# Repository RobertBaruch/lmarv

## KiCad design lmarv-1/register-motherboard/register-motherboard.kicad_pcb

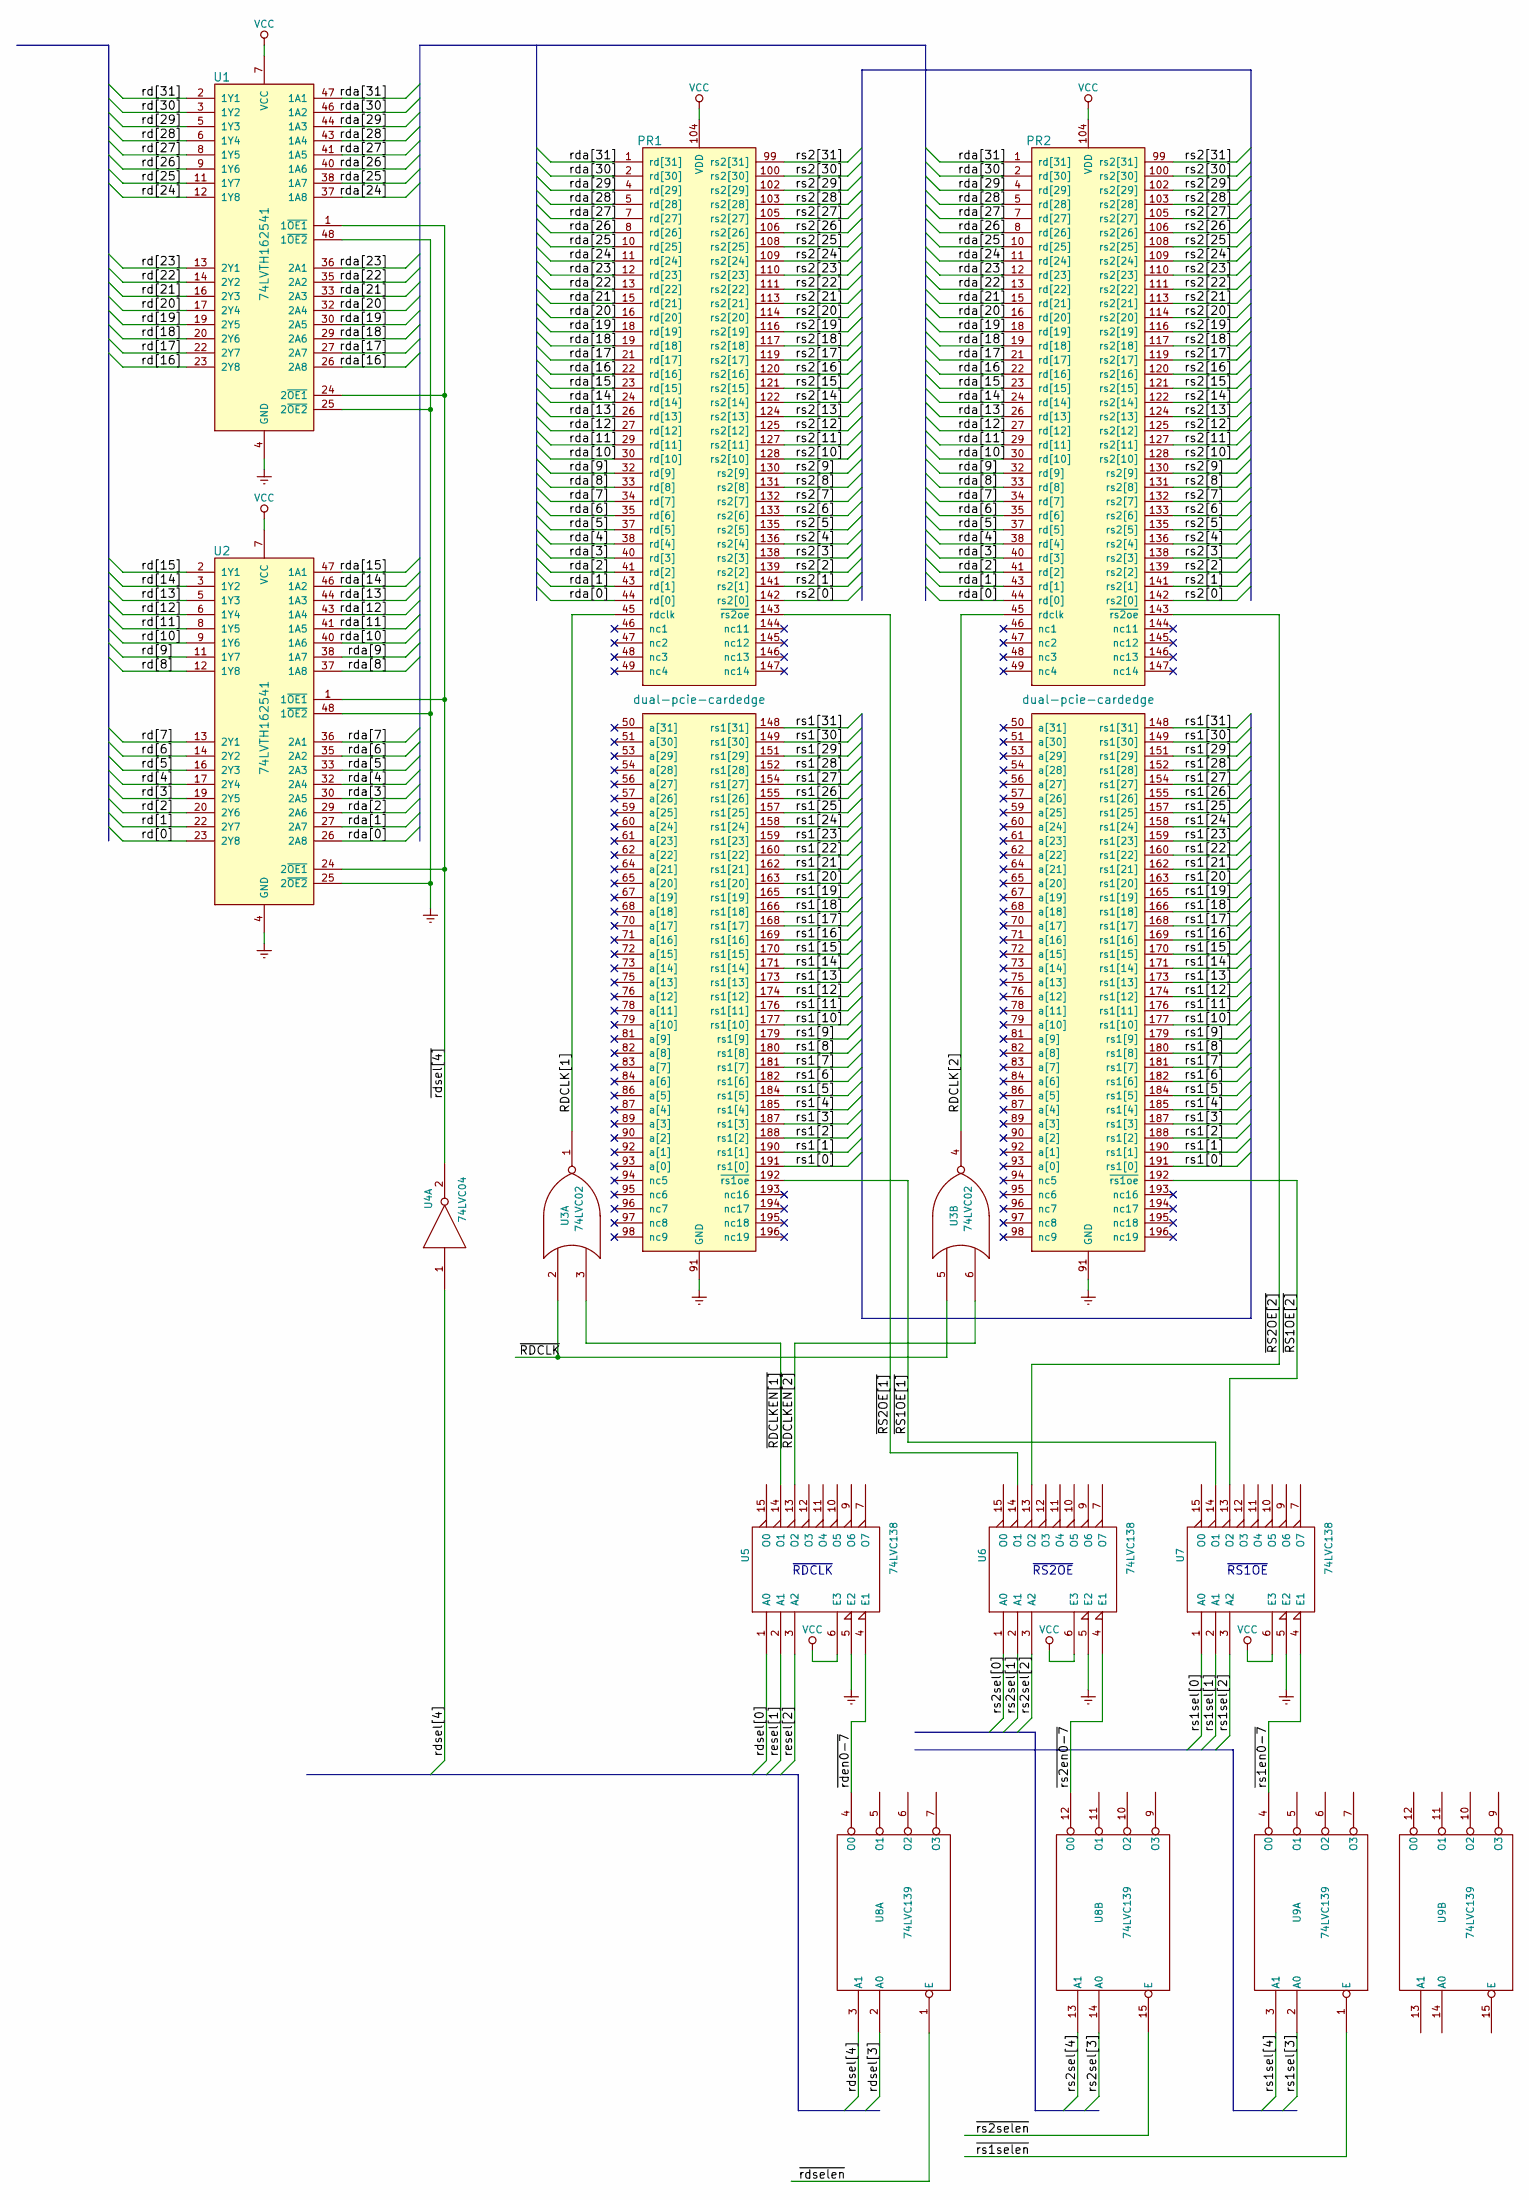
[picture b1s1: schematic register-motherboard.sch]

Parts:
PR1, PR2: dual-pcie-cardedge; 2pci_express_slot
U1, U2: 74LVTH162541; SSOP-48_7.5x15.9mm_Pitch0.635mm
U3: 74LVC02; SOIC-8_3.9x4.9mm_Pitch1.27mm
U4: 74LVC04; SO-4_4.4x2.3mm_Pitch1.27mm
U5, U6, U7: 74LVC138; SOIC-16_3.9x9.9mm_Pitch1.27mm
U8, U9: 74LVC139; SOIC-16_3.9x9.9mm_Pitch1.27mm

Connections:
/RDCLK[1]: PR1.45 (rdclk), U3.1
/RDCLK[2]: PR2.45 (rdclk), U3.4
/rd[0]: U2.23 (2Y8)
/rd[1]: U2.22 (2Y7)
/rd[2]: U2.20 (2Y6)
/rd[3]: U2.19 (2Y5)
/rd[4]: U2.17 (2Y4)
/rd[5]: U2.16 (2Y3)
/rd[6]: U2.14 (2Y2)
/rd[7]: U2.13 (2Y1)
/rd[8]: U2.12 (1Y8)
/rd[9]: U2.11 (1Y7)
/rd[10]: U2.9 (1Y6)
/rd[11]: U2.8 (1Y5)
/rd[12]: U2.6 (1Y4)
/rd[13]: U2.5 (1Y3)
/rd[14]: U2.3 (1Y2)
/rd[15]: U2.2 (1Y1)
/rd[16]: U1.23 (2Y8)
/rd[17]: U1.22 (2Y7)
/rd[18]: U1.20 (2Y6)
/rd[19]: U1.19 (2Y5)
/rd[20]: U1.17 (2Y4)
/rd[21]: U1.16 (2Y3)
/rd[22]: U1.14 (2Y2)
/rd[23]: U1.13 (2Y1)
/rd[24]: U1.12 (1Y8)
/rd[25]: U1.11 (1Y7)
/rd[26]: U1.9 (1Y6)
/rd[27]: U1.8 (1Y5)
/rd[28]: U1.6 (1Y4)
/rd[29]: U1.5 (1Y3)
/rd[30]: U1.3 (1Y2)
/rd[31]: U1.2 (1Y1)
/rda[0]: PR1.44 (rd[0]), PR2.44 (rd[0]), U2.26 (2A8)
/rda[1]: PR1.43 (rd[1]), PR2.43 (rd[1]), U2.27 (2A7)
/rda[2]: PR1.41 (rd[2]), PR2.41 (rd[2]), U2.29 (2A6)
/rda[3]: PR1.40 (rd[3]), PR2.40 (rd[3]), U2.30 (2A5)
/rda[4]: PR1.38 (rd[4]), PR2.38 (rd[4]), U2.32 (2A4)
/rda[5]: PR1.37 (rd[5]), PR2.37 (rd[5]), U2.33 (2A3)
/rda[6]: PR1.35 (rd[6]), PR2.35 (rd[6]), U2.35 (2A2)
/rda[7]: PR1.34 (rd[7]), PR2.34 (rd[7]), U2.36 (2A1)
/rda[8]: PR1.33 (rd[8]), PR2.33 (rd[8]), U2.37 (1A8)
/rda[9]: PR1.32 (rd[9]), PR2.32 (rd[9]), U2.38 (1A7)
/rda[10]: PR1.30 (rd[10]), PR2.30 (rd[10]), U2.40 (1A6)
/rda[11]: PR1.29 (rd[11]), PR2.29 (rd[11]), U2.41 (1A5)
/rda[12]: PR1.27 (rd[12]), PR2.27 (rd[12]), U2.43 (1A4)
/rda[13]: PR1.26 (rd[13]), PR2.26 (rd[13]), U2.44 (1A3)
/rda[14]: PR1.24 (rd[14]), PR2.24 (rd[14]), U2.46 (1A2)
/rda[15]: PR1.23 (rd[15]), PR2.23 (rd[15]), U2.47 (1A1)
/rda[16]: PR1.22 (rd[16]), PR2.22 (rd[16]), U1.26 (2A8)
/rda[17]: PR1.21 (rd[17]), PR2.21 (rd[17]), U1.27 (2A7)
/rda[18]: PR1.19 (rd[18]), PR2.19 (rd[18]), U1.29 (2A6)
/rda[19]: PR1.18 (rd[19]), PR2.18 (rd[19]), U1.30 (2A5)
/rda[20]: PR1.16 (rd[20]), PR2.16 (rd[20]), U1.32 (2A4)
/rda[21]: PR1.15 (rd[21]), PR2.15 (rd[21]), U1.33 (2A3)
/rda[22]: PR1.13 (rd[22]), PR2.13 (rd[22]), U1.35 (2A2)
/rda[23]: PR1.12 (rd[23]), PR2.12 (rd[23]), U1.36 (2A1)
/rda[24]: PR1.11 (rd[24]), PR2.11 (rd[24]), U1.37 (1A8)
/rda[25]: PR1.10 (rd[25]), PR2.10 (rd[25]), U1.38 (1A7)
/rda[26]: PR1.8 (rd[26]), PR2.8 (rd[26]), U1.40 (1A6)
/rda[27]: PR1.7 (rd[27]), PR2.7 (rd[27]), U1.41 (1A5)
/rda[28]: PR1.5 (rd[28]), PR2.5 (rd[28]), U1.43 (1A4)
/rda[29]: PR1.4 (rd[29]), PR2.4 (rd[29]), U1.44 (1A3)
/rda[30]: PR1.2 (rd[30]), PR2.2 (rd[30]), U1.46 (1A2)
/rda[31]: PR1.1 (rd[31]), PR2.1 (rd[31]), U1.47 (1A1)
/rdsel[0]: U5.1 (A0)
/rdsel[3]: U8.2 (A0)
/rdsel[4]: U4.1, U8.3 (A1)
/resel[1]: U5.2 (A1)
/resel[2]: U5.3 (A2)
/rs1[0]: PR1.191 (rs1[0]), PR2.191 (rs1[0])
/rs1[1]: PR1.190 (rs1[1]), PR2.190 (rs1[1])
/rs1[2]: PR1.188 (rs1[2]), PR2.188 (rs1[2])
/rs1[3]: PR1.187 (rs1[3]), PR2.187 (rs1[3])
/rs1[4]: PR1.185 (rs1[4]), PR2.185 (rs1[4])
/rs1[5]: PR1.184 (rs1[5]), PR2.184 (rs1[5])
/rs1[6]: PR1.182 (rs1[6]), PR2.182 (rs1[6])
/rs1[7]: PR1.181 (rs1[7]), PR2.181 (rs1[7])
/rs1[8]: PR1.180 (rs1[8]), PR2.180 (rs1[8])
/rs1[9]: PR1.179 (rs1[9]), PR2.179 (rs1[9])
/rs1[10]: PR1.177 (rs1[10]), PR2.177 (rs1[10])
/rs1[11]: PR1.176 (rs1[11]), PR2.176 (rs1[11])
/rs1[12]: PR1.174 (rs1[12]), PR2.174 (rs1[12])
/rs1[13]: PR1.173 (rs1[13]), PR2.173 (rs1[13])
/rs1[14]: PR1.171 (rs1[14]), PR2.171 (rs1[14])
/rs1[15]: PR1.170 (rs1[15]), PR2.170 (rs1[15])
/rs1[16]: PR1.169 (rs1[16]), PR2.169 (rs1[16])
/rs1[17]: PR1.168 (rs1[17]), PR2.168 (rs1[17])
/rs1[18]: PR1.166 (rs1[18]), PR2.166 (rs1[18])
/rs1[19]: PR1.165 (rs1[19]), PR2.165 (rs1[19])
/rs1[20]: PR1.163 (rs1[20]), PR2.163 (rs1[20])
/rs1[21]: PR1.162 (rs1[21]), PR2.162 (rs1[21])
/rs1[22]: PR1.160 (rs1[22]), PR2.160 (rs1[22])
/rs1[23]: PR1.159 (rs1[23]), PR2.159 (rs1[23])
/rs1[24]: PR1.158 (rs1[24]), PR2.158 (rs1[24])
/rs1[25]: PR1.157 (rs1[25]), PR2.157 (rs1[25])
/rs1[26]: PR1.155 (rs1[26]), PR2.155 (rs1[26])
/rs1[27]: PR1.154 (rs1[27]), PR2.154 (rs1[27])
/rs1[28]: PR1.152 (rs1[28]), PR2.152 (rs1[28])
/rs1[29]: PR1.151 (rs1[29]), PR2.151 (rs1[29])
/rs1[30]: PR1.149 (rs1[30]), PR2.149 (rs1[30])
/rs1[31]: PR1.148 (rs1[31]), PR2.148 (rs1[31])
/rs1sel[0]: U7.1 (A0)
/rs1sel[1]: U7.2 (A1)
/rs1sel[2]: U7.3 (A2)
/rs1sel[3]: U9.2 (A0)
/rs1sel[4]: U9.3 (A1)
/rs2[0]: PR1.142 (rs2[0]), PR2.142 (rs2[0])
/rs2[1]: PR1.141 (rs2[1]), PR2.141 (rs2[1])
/rs2[2]: PR1.139 (rs2[2]), PR2.139 (rs2[2])
/rs2[3]: PR1.138 (rs2[3]), PR2.138 (rs2[3])
/rs2[4]: PR1.136 (rs2[4]), PR2.136 (rs2[4])
/rs2[5]: PR1.135 (rs2[5]), PR2.135 (rs2[5])
/rs2[6]: PR1.133 (rs2[6]), PR2.133 (rs2[6])
/rs2[7]: PR1.132 (rs2[7]), PR2.132 (rs2[7])
/rs2[8]: PR1.131 (rs2[8]), PR2.131 (rs2[8])
/rs2[9]: PR1.130 (rs2[9]), PR2.130 (rs2[9])
/rs2[10]: PR1.128 (rs2[10]), PR2.128 (rs2[10])
/rs2[11]: PR1.127 (rs2[11]), PR2.127 (rs2[11])
/rs2[12]: PR1.125 (rs2[12]), PR2.125 (rs2[12])
/rs2[13]: PR1.124 (rs2[13]), PR2.124 (rs2[13])
/rs2[14]: PR1.122 (rs2[14]), PR2.122 (rs2[14])
/rs2[15]: PR1.121 (rs2[15]), PR2.121 (rs2[15])
/rs2[16]: PR1.120 (rs2[16]), PR2.120 (rs2[16])
/rs2[17]: PR1.119 (rs2[17]), PR2.119 (rs2[17])
/rs2[18]: PR1.117 (rs2[18]), PR2.117 (rs2[18])
/rs2[19]: PR1.116 (rs2[19]), PR2.116 (rs2[19])
/rs2[20]: PR1.114 (rs2[20]), PR2.114 (rs2[20])
/rs2[21]: PR1.113 (rs2[21]), PR2.113 (rs2[21])
/rs2[22]: PR1.111 (rs2[22]), PR2.111 (rs2[22])
/rs2[23]: PR1.110 (rs2[23]), PR2.110 (rs2[23])
/rs2[24]: PR1.109 (rs2[24]), PR2.109 (rs2[24])
/rs2[25]: PR1.108 (rs2[25]), PR2.108 (rs2[25])
/rs2[26]: PR1.106 (rs2[26]), PR2.106 (rs2[26])
/rs2[27]: PR1.105 (rs2[27]), PR2.105 (rs2[27])
/rs2[28]: PR1.103 (rs2[28]), PR2.103 (rs2[28])
/rs2[29]: PR1.102 (rs2[29]), PR2.102 (rs2[29])
/rs2[30]: PR1.100 (rs2[30]), PR2.100 (rs2[30])
/rs2[31]: PR1.99 (rs2[31]), PR2.99 (rs2[31])
/rs2sel[0]: U6.1 (A0)
/rs2sel[1]: U6.2 (A1)
/rs2sel[2]: U6.3 (A2)
/rs2sel[3]: U8.14 (A0)
/rs2sel[4]: U8.13 (A1)
/~RDCLK: U3.2, U3.5
/~RDCLKEN[1]: U3.3, U5.14 (O1)
/~RDCLKEN[2]: U3.6, U5.13 (O2)
/~RS1OE[1]: PR1.192 (~rs1oe), U7.14 (O1)
/~RS1OE[2]: PR2.192 (~rs1oe), U7.13 (O2)
/~RS2OE[1]: PR1.143 (~rs2oe), U6.14 (O1)
/~RS2OE[2]: PR2.143 (~rs2oe), U6.13 (O2)
/~rden0-7: U5.4 (E1), U8.4 (O0)
/~rdsel[4]: U1.1 (1~OE1), U1.24 (2~OE1), U2.1 (1~OE1), U2.24 (2~OE1), U4.2
/~rdselen: U8.1 (E)
/~rs1en0-7: U7.4 (E1), U9.4 (O0)
/~rs1selen: U9.1 (E)
/~rs2en0-7: U6.4 (E1), U8.12 (O0)
/~rs2selen: U8.15 (E)
GND: U3.7 (GND), U5.8 (GND), U6.8 (GND), U7.8 (GND), U8.8 (GND), U9.8 (GND)
GNDREF: PR1.3 (GND), PR1.9 (GND), PR1.14 (GND), PR1.20 (GND), PR1.25 (GND), PR1.31 (GND), PR1.36 (GND), PR1.42 (GND), PR1.52 (GND), PR1.58 (GND), PR1.63 (GND), PR1.69 (GND), PR1.74 (GND), PR1.80 (GND), PR1.85 (GND), PR1.91 (GND), PR1.101 (GND), PR1.107 (GND), PR1.112 (GND), PR1.118 (GND), PR1.123 (GND), PR1.129 (GND), PR1.134 (GND), PR1.140 (GND), PR1.150 (GND), PR1.156 (GND), PR1.161 (GND), PR1.167 (GND), PR1.172 (GND), PR1.178 (GND), PR1.183 (GND), PR1.189 (GND), PR2.3 (GND), PR2.9 (GND), PR2.14 (GND), PR2.20 (GND), PR2.25 (GND), PR2.31 (GND), PR2.36 (GND), PR2.42 (GND), PR2.52 (GND), PR2.58 (GND), PR2.63 (GND), PR2.69 (GND), PR2.74 (GND), PR2.80 (GND), PR2.85 (GND), PR2.91 (GND), PR2.101 (GND), PR2.107 (GND), PR2.112 (GND), PR2.118 (GND), PR2.123 (GND), PR2.129 (GND), PR2.134 (GND), PR2.140 (GND), PR2.150 (GND), PR2.156 (GND), PR2.161 (GND), PR2.167 (GND), PR2.172 (GND), PR2.178 (GND), PR2.183 (GND), PR2.189 (GND), U1.4 (GND), U1.10 (GND), U1.15 (GND), U1.21 (GND), U1.25 (2~OE2), U1.28 (GND), U1.34 (GND), U1.39 (GND), U1.45 (GND), U1.48 (1~OE2), U2.4 (GND), U2.10 (GND), U2.15 (GND), U2.21 (GND), U2.25 (2~OE2), U2.28 (GND), U2.34 (GND), U2.39 (GND), U2.45 (GND), U2.48 (1~OE2), U5.5 (E2), U6.5 (E2), U7.5 (E2)
VCC: PR1.6 (VDD), PR1.17 (VDD), PR1.28 (VDD), PR1.39 (VDD), PR1.55 (VDD), PR1.66 (VDD), PR1.77 (VDD), PR1.88 (VDD), PR1.104 (VDD), PR1.115 (VDD), PR1.126 (VDD), PR1.137 (VDD), PR1.153 (VDD), PR1.164 (VDD), PR1.175 (VDD), PR1.186 (VDD), PR2.6 (VDD), PR2.17 (VDD), PR2.28 (VDD), PR2.39 (VDD), PR2.55 (VDD), PR2.66 (VDD), PR2.77 (VDD), PR2.88 (VDD), PR2.104 (VDD), PR2.115 (VDD), PR2.126 (VDD), PR2.137 (VDD), PR2.153 (VDD), PR2.164 (VDD), PR2.175 (VDD), PR2.186 (VDD), U1.7 (VCC), U1.18 (VCC), U1.31 (VCC), U1.42 (VCC), U2.7 (VCC), U2.18 (VCC), U2.31 (VCC), U2.42 (VCC), U5.6 (E3), U5.16 (VCC), U6.6 (E3), U6.16 (VCC), U7.6 (E3), U7.16 (VCC), U8.16 (VCC), U9.16 (VCC)

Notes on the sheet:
~RS1OE
~RS2OE
~RDCLK

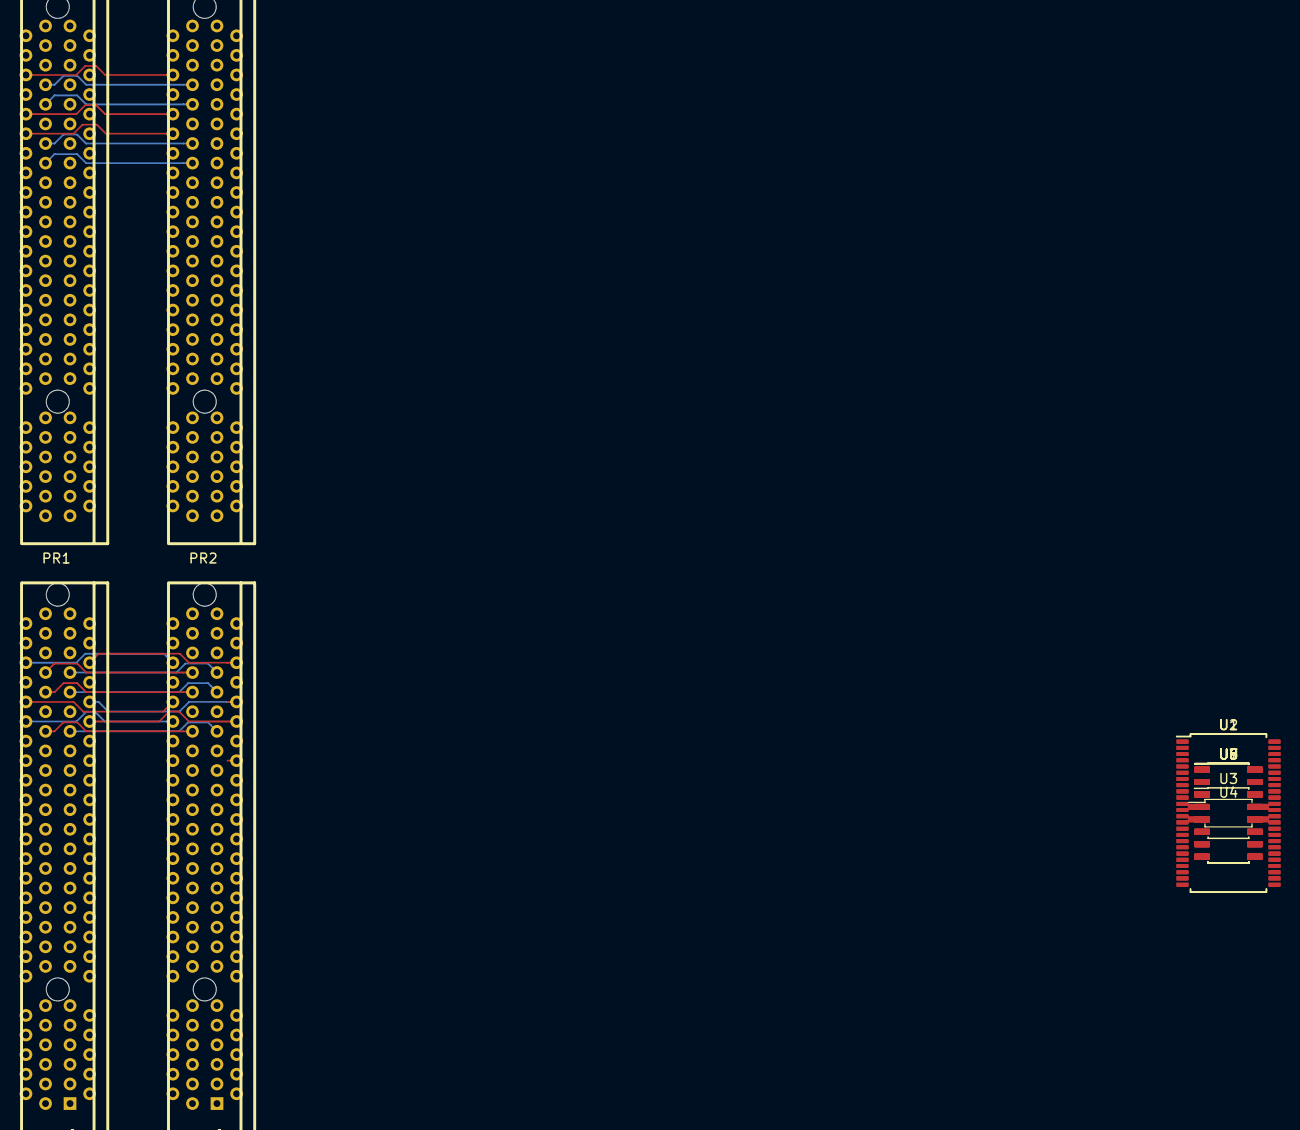
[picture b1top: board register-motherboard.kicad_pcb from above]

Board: 4 copper layers, 11 parts (0 on the bottom side), 113 nets.

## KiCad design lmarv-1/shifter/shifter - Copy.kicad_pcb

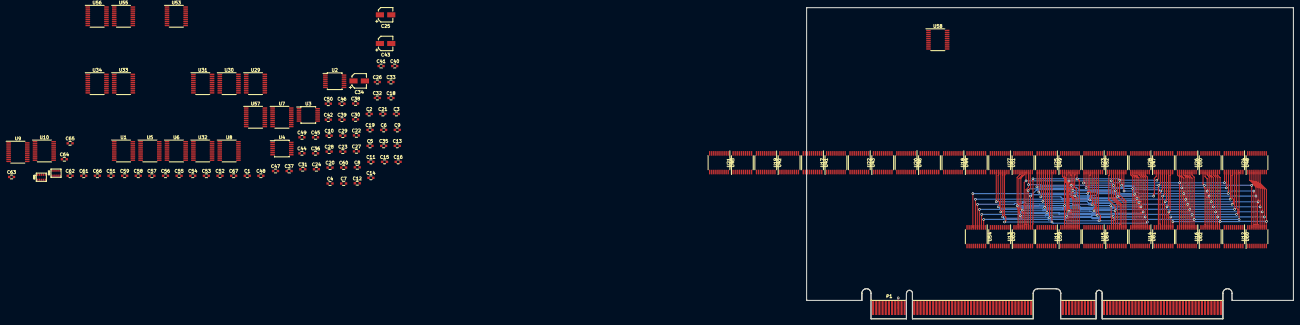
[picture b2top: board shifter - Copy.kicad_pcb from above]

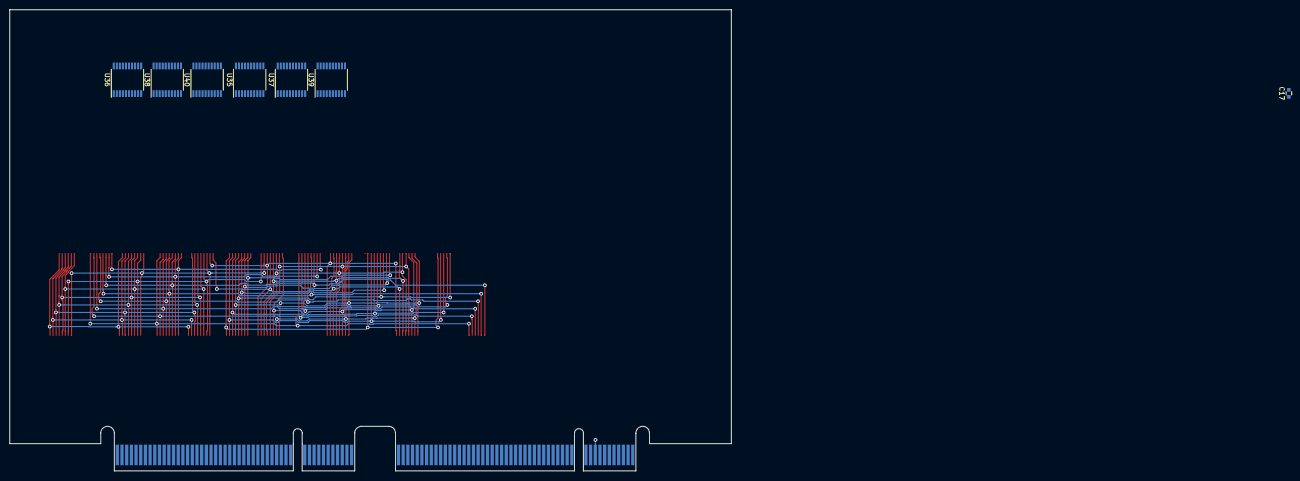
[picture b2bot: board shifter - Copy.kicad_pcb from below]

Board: 4 copper layers, 154.0 x 98.4 mm, 134 parts (7 on the bottom side), 222 nets.

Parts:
C1, C2, C3, C4, C5, C6, C7, C8, C9, C10, C11, C12, C13, C14, C15, C16, C17, C18, C19, C20, C21, C22, C23, C24, C26, C27, C28, C29, C30, C31, C32, C33, C35, C36, C37, C38, C39, C40, C41, C42, C44, C45, C46, C47, C48, C49, C50, C51, C52, C53, C54, C55, C56, C57, C58, C59, C60, C61, C62, C63, C64, C65, C66, C67: 100n; C_0603
C25, C34, C43: 10u; CP_Elec_4x4.5
P1: dual-pcie-cardedge; PCI-EXPRESS
RN1, RN2: RPACK8; YC158
U1, U5, U6, U7, U8, U9, U10, U11, U12, U13, U14, U15, U16, U17, U18, U19, U20, U21, U22, U23, U24, U25, U26, U27, U28, U29, U30, U31, U32, U33, U34, U35, U36, U37, U38, U39, U40, U41, U42, U43, U44, U45, U46, U47, U48, U49, U50, U51, U52, U53, U54, U55, U56, U57, U58, U59, U60, U61, U62, U63, U64: 74LVC541; TSSOP-20_4.4x6.5mm_Pitch0.65mm
U2: 74LVC04; TSSOP-14_4.4x5mm_Pitch0.65mm
U3: 74LVC08; TSSOP-14_4.4x5mm_Pitch0.65mm
U4: 74LVC32; TSSOP-14_4.4x5mm_Pitch0.65mm

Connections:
/msb: U3.3, U3.4, U3.5, U3.9, U3.10, U3.12, U3.13, U9.9, U21.2, U21.3, U33.6, U33.7, U33.8, U33.9
/msb': U3.6, U57.2, U57.3, U57.4, U57.5, U57.6, U57.7, U57.8, U57.9
/msb'': U3.8, U58.2, U58.3, U58.4, U58.5, U58.6, U58.7, U58.8, U58.9
/msb''': U3.11, U45.2, U45.3, U45.4, U45.5, U45.6, U45.7, U45.8, U45.9
/rd[0]: P1.71, U60.18, U62.18, U64.18
/rd[1]: P1.70, U60.17, U62.17, U64.17
/rd[2]: P1.68, U60.16, U62.16, U64.16
/rd[3]: P1.67, U60.15, U62.15, U64.15
/rd[4]: P1.65, U60.14, U62.14, U64.14
/rd[5]: P1.64, U60.13, U62.13, U64.13
/rd[6]: P1.62, U60.12, U62.12, U64.12
/rd[7]: P1.61, U60.11, U62.11, U64.11
/rd[8]: P1.60, U59.18, U61.18, U63.18
/rd[9]: P1.59, U59.17, U61.17, U63.17
/rd[10]: P1.57, U59.16, U61.16, U63.16
/rd[11]: P1.56, U59.15, U61.15, U63.15
/rd[12]: P1.54, U59.14, U61.14, U63.14
/rd[13]: P1.53, U59.13, U61.13, U63.13
/rd[14]: P1.51, U59.12, U61.12, U63.12
/rd[15]: P1.50, U59.11, U61.11, U63.11
/rd[16]: P1.22, U54.18, U56.18, U58.18
/rd[17]: P1.21, U54.17, U56.17, U58.17
/rd[18]: P1.19, U54.16, U56.16, U58.16
/rd[19]: P1.18, U54.15, U56.15, U58.15
/rd[20]: P1.16, U54.14, U56.14, U58.14
/rd[21]: P1.15, U54.13, U56.13, U58.13
/rd[22]: P1.13, U54.12, U56.12, U58.12
/rd[23]: P1.12, U54.11, U56.11, U58.11
/rd[24]: P1.11, U53.18, U55.18, U57.18
/rd[25]: P1.10, U53.17, U55.17, U57.17
/rd[26]: P1.8, U53.16, U55.16, U57.16
/rd[27]: P1.7, U53.15, U55.15, U57.15
/rd[28]: P1.5, U53.14, U55.14, U57.14
/rd[29]: P1.4, U53.13, U55.13, U57.13
/rd[30]: P1.2, U53.12, U55.12, U57.12
/rd[31]: P1.1, U53.11, U55.11, U57.11
/rs1[0]: P1.176, U12.8, U14.9
/rs1[1]: P1.174, U12.7, U14.8, U16.9
/rs1[2]: P1.173, U12.6, U14.7, U16.8
/rs1[3]: P1.171, U12.5, U14.6, U16.7
/rs1[4]: P1.170, U12.4, U14.5, U16.6
/rs1[5]: P1.169, U12.3, U14.4, U16.5
/rs1[6]: P1.168, U12.2, U14.3, U16.4
/rs1[7]: P1.166, U11.9, U14.2, U16.3
/rs1[8]: P1.165, U11.8, U13.9, U16.2
/rs1[9]: P1.163, U11.7, U13.8, U15.9
/rs1[10]: P1.162, U11.6, U13.7, U15.8
/rs1[11]: P1.160, U11.5, U13.6, U15.7
/rs1[12]: P1.159, U11.4, U13.5, U15.6
/rs1[13]: P1.158, U11.3, U13.4, U15.5
/rs1[14]: P1.157, U11.2, U13.3, U15.4
/rs1[15]: P1.155, U6.2, U13.2, U15.3
/rs1[16]: P1.120, U6.3, U8.2, U15.2
/rs1[17]: P1.119, U6.4, U8.3, U10.2
/rs1[18]: P1.117, U6.5, U8.4, U10.3
/rs1[19]: P1.116, U6.6, U8.5, U10.4
/rs1[20]: P1.114, U6.7, U8.6, U10.5
/rs1[21]: P1.113, U6.8, U8.7, U10.6
/rs1[22]: P1.111, U6.9, U8.8, U10.7
/rs1[23]: P1.110, U5.2, U8.9, U10.8
/rs1[24]: P1.109, U5.3, U7.2, U10.9
/rs1[25]: P1.108, U5.4, U7.3, U9.2
/rs1[26]: P1.106, U5.5, U7.4, U9.3
/rs1[27]: P1.105, U5.6, U7.5, U9.4
/rs1[28]: P1.103, U5.7, U7.6, U9.5
/rs1[29]: P1.102, U5.8, U7.7, U9.6
/rs1[30]: P1.100, U5.9, U7.8, U9.7
/rs1[31]: P1.99, U3.1, U7.9, U9.8
/rs2[0]': P1.93, U1.7
/rs2[1]': P1.92, U1.6
/rs2[2]': P1.90, U1.5
/rs2[3]': P1.89, U1.4
/rs2[4]': P1.87, U1.3
/s1[0]: U12.11, U14.11, U16.11, U24.7, U26.9
/s1[1]: U12.12, U14.12, U16.12, U24.6, U26.8
/s1[2]: U12.13, U14.13, U16.13, U24.5, U26.7, U28.9
/s1[3]: U12.14, U14.14, U16.14, U24.4, U26.6, U28.8
/s1[4]: U12.15, U14.15, U16.15, U24.3, U26.5, U28.7
/s1[5]: U12.16, U14.16, U16.16, U24.2, U26.4, U28.6
/s1[6]: U12.17, U14.17, U16.17, U23.9, U26.3, U28.5
/s1[7]: U12.18, U14.18, U16.18, U23.8, U26.2, U28.4
/s1[8]: U11.11, U13.11, U15.11, U23.7, U25.9, U28.3
/s1[9]: U11.12, U13.12, U15.12, U23.6, U25.8, U28.2
/s1[10]: U11.13, U13.13, U15.13, U23.5, U25.7, U27.9
/s1[11]: U11.14, U13.14, U15.14, U23.4, U25.6, U27.8
/s1[12]: U11.15, U13.15, U15.15, U23.3, U25.5, U27.7
/s1[13]: U11.16, U13.16, U15.16, U23.2, U25.4, U27.6
/s1[14]: U11.17, U13.17, U15.17, U18.9, U25.3, U27.5
/s1[15]: U11.18, U13.18, U15.18, U18.8, U25.2, U27.4
/s1[16]: U6.18, U8.18, U10.18, U18.7, U20.9, U27.3
/s1[17]: U6.17, U8.17, U10.17, U18.6, U20.8, U27.2
/s1[18]: U6.16, U8.16, U10.16, U18.5, U20.7, U22.9
/s1[19]: U6.15, U8.15, U10.15, U18.4, U20.6, U22.8
/s1[20]: U6.14, U8.14, U10.14, U18.3, U20.5, U22.7
/s1[21]: U6.13, U8.13, U10.13, U18.2, U20.4, U22.6
/s1[22]: U6.12, U8.12, U10.12, U17.9, U20.3, U22.5
/s1[23]: U6.11, U8.11, U10.11, U17.8, U20.2, U22.4
/s1[24]: U5.18, U7.18, U9.18, U17.7, U19.9, U22.3
/s1[25]: U5.17, U7.17, U9.17, U17.6, U19.8, U22.2
/s1[26]: U5.16, U7.16, U9.16, U17.5, U19.7, U21.9
/s1[27]: U5.15, U7.15, U9.15, U17.4, U19.6, U21.8
/s1[28]: U5.14, U7.14, U9.14, U17.3, U19.5, U21.7
/s1[29]: U5.13, U7.13, U9.13, U17.2, U19.4, U21.6
/s1[30]: U5.12, U7.12, U9.12, U19.3, U21.5
/s1[31]: U5.11, U7.11, U9.11, U19.2, U21.4
/s2[0]: U24.11, U26.11, U28.11, U36.6, U38.2
/s2[1]: U24.12, U26.12, U28.12, U36.7, U38.3
/s2[2]: U24.13, U26.13, U28.13, U36.8, U38.4
/s2[3]: U24.14, U26.14, U28.14, U36.9, U38.5
/s2[4]: U24.15, U26.15, U28.15, U35.2, U38.6, U40.2
/s2[5]: U24.16, U26.16, U28.16, U35.3, U38.7, U40.3
/s2[6]: U24.17, U26.17, U28.17, U35.4, U38.8, U40.4
/s2[7]: U24.18, U26.18, U28.18, U35.5, U38.9, U40.5
/s2[8]: U23.11, U25.11, U27.11, U35.6, U37.2, U40.6
/s2[9]: U23.12, U25.12, U27.12, U35.7, U37.3, U40.7
/s2[10]: U23.13, U25.13, U27.13, U35.8, U37.4, U40.8
/s2[11]: U23.14, U25.14, U27.14, U35.9, U37.5, U40.9
/s2[12]: U23.15, U25.15, U27.15, U30.2, U37.6, U39.2
/s2[13]: U23.16, U25.16, U27.16, U30.3, U37.7, U39.3
/s2[14]: U23.17, U25.17, U27.17, U30.4, U37.8, U39.4
/s2[15]: U23.18, U25.18, U27.18, U30.5, U37.9, U39.5
/s2[16]: U18.11, U20.11, U22.11, U30.6, U32.2, U39.6
/s2[17]: U18.12, U20.12, U22.12, U30.7, U32.3, U39.7
/s2[18]: U18.13, U20.13, U22.13, U30.8, U32.4, U39.8
/s2[19]: U18.14, U20.14, U22.14, U30.9, U32.5, U39.9
/s2[20]: U18.15, U20.15, U22.15, U29.2, U32.6, U34.2
/s2[21]: U18.16, U20.16, U22.16, U29.3, U32.7, U34.3
/s2[22]: U18.17, U20.17, U22.17, U29.4, U32.8, U34.4
/s2[23]: U18.18, U20.18, U22.18, U29.5, U32.9, U34.5
/s2[24]: U17.11, U19.11, U21.11, U29.6, U31.2, U34.6
/s2[25]: U17.12, U19.12, U21.12, U29.7, U31.3, U34.7
/s2[26]: U17.13, U19.13, U21.13, U29.8, U31.4, U34.8
/s2[27]: U17.14, U19.14, U21.14, U29.9, U31.5, U34.9
/s2[28]: U17.15, U19.15, U21.15, U31.6, U33.2
/s2[29]: U17.16, U19.16, U21.16, U31.7, U33.3
/s2[30]: U17.17, U19.17, U21.17, U31.8, U33.4
/s2[31]: U17.18, U19.18, U21.18, U31.9, U33.5
/s4[0]: U36.18, U38.18, U40.18, U47.2, U50.2
/s4[1]: U36.17, U38.17, U40.17, U47.3, U50.3
/s4[2]: U36.16, U38.16, U40.16, U47.4, U50.4
/s4[3]: U36.15, U38.15, U40.15, U47.5, U50.5
/s4[4]: U36.14, U38.14, U40.14, U47.6, U50.6
/s4[5]: U36.13, U38.13, U40.13, U47.7, U50.7
/s4[6]: U36.12, U38.12, U40.12, U47.8, U50.8
/s4[7]: U36.11, U38.11, U40.11, U47.9, U50.9
/s4[8]: U35.18, U37.18, U39.18, U42.2, U49.2, U52.2
/s4[9]: U35.17, U37.17, U39.17, U42.3, U49.3, U52.3
/s4[10]: U35.16, U37.16, U39.16, U42.4, U49.4, U52.4
/s4[11]: U35.15, U37.15, U39.15, U42.5, U49.5, U52.5
/s4[12]: U35.14, U37.14, U39.14, U42.6, U49.6, U52.6
/s4[13]: U35.13, U37.13, U39.13, U42.7, U49.7, U52.7
/s4[14]: U35.12, U37.12, U39.12, U42.8, U49.8, U52.8
/s4[15]: U35.11, U37.11, U39.11, U42.9, U49.9, U52.9
/s4[16]: U30.18, U32.18, U34.18, U41.2, U44.2, U51.2
/s4[17]: U30.17, U32.17, U34.17, U41.3, U44.3, U51.3
/s4[18]: U30.16, U32.16, U34.16, U41.4, U44.4, U51.4
/s4[19]: U30.15, U32.15, U34.15, U41.5, U44.5, U51.5
/s4[20]: U30.14, U32.14, U34.14, U41.6, U44.6, U51.6
/s4[21]: U30.13, U32.13, U34.13, U41.7, U44.7, U51.7
/s4[22]: U30.12, U32.12, U34.12, U41.8, U44.8, U51.8
/s4[23]: U30.11, U32.11, U34.11, U41.9, U44.9, U51.9
/s4[24]: U29.18, U31.18, U33.18, U43.2, U46.2
/s4[25]: U29.17, U31.17, U33.17, U43.3, U46.3
/s4[26]: U29.16, U31.16, U33.16, U43.4, U46.4
/s4[27]: U29.15, U31.15, U33.15, U43.5, U46.5
/s4[28]: U29.14, U31.14, U33.14, U43.6, U46.6
/s4[29]: U29.13, U31.13, U33.13, U43.7, U46.7
/s4[30]: U29.12, U31.12, U33.12, U43.8, U46.8
/s4[31]: U29.11, U31.11, U33.11, U43.9, U46.9
/s8[0]: U48.18, U50.18, U52.18, U54.2, U62.2
/s8[1]: U48.17, U50.17, U52.17, U54.3, U62.3
/s8[2]: U48.16, U50.16, U52.16, U54.4, U62.4
/s8[3]: U48.15, U50.15, U52.15, U54.5, U62.5
/s8[4]: U48.14, U50.14, U52.14, U54.6, U62.6
/s8[5]: U48.13, U50.13, U52.13, U54.7, U62.7
/s8[6]: U48.12, U50.12, U52.12, U54.8, U62.8
/s8[7]: U48.11, U50.11, U52.11, U54.9, U62.9
/s8[8]: U47.18, U49.18, U51.18, U53.2, U61.2
/s8[9]: U47.17, U49.17, U51.17, U53.3, U61.3
/s8[10]: U47.16, U49.16, U51.16, U53.4, U61.4
/s8[11]: U47.15, U49.15, U51.15, U53.5, U61.5
/s8[12]: U47.14, U49.14, U51.14, U53.6, U61.6
/s8[13]: U47.13, U49.13, U51.13, U53.7, U61.7
/s8[14]: U47.12, U49.12, U51.12, U53.8, U61.8
/s8[15]: U47.11, U49.11, U51.11, U53.9, U61.9
/s8[16]: U42.18, U44.18, U46.18, U56.2, U64.2
/s8[17]: U42.17, U44.17, U46.17, U56.3, U64.3
/s8[18]: U42.16, U44.16, U46.16, U56.4, U64.4
/s8[19]: U42.15, U44.15, U46.15, U56.5, U64.5
/s8[20]: U42.14, U44.14, U46.14, U56.6, U64.6
/s8[21]: U42.13, U44.13, U46.13, U56.7, U64.7
/s8[22]: U42.12, U44.12, U46.12, U56.8, U64.8
/s8[23]: U42.11, U44.11, U46.11, U56.9, U64.9
/s8[24]: U41.18, U43.18, U45.18, U55.2, U63.2
/s8[25]: U41.17, U43.17, U45.17, U55.3, U63.3
/s8[26]: U41.16, U43.16, U45.16, U55.4, U63.4
/s8[27]: U41.15, U43.15, U45.15, U55.5, U63.5
/s8[28]: U41.14, U43.14, U45.14, U55.6, U63.6
/s8[29]: U41.13, U43.13, U45.13, U55.7, U63.7
/s8[30]: U41.12, U43.12, U45.12, U55.8, U63.8
/s8[31]: U41.11, U43.11, U45.11, U55.9, U63.9
/shift1: RN1.1, U1.13, U2.1, U7.19, U8.19, U13.1, U14.1
/shift2: RN1.2, U1.14, U2.3, U19.1, U20.1, U25.1, U26.1
/shift4: RN1.3, U1.15, U2.5, U31.19, U32.19, U37.19, U38.19
/shift8: RN1.4, U1.16, U2.9, U43.19, U44.19, U49.19, U50.19
/shift16: RN1.6, U1.17, U2.11, U4.5
/shift_arith: RN1.8, U1.12, U3.2
/shift_arith': P1.192, U1.8
/~noshift_16_oe: RN2.1, U4.6, U55.19, U56.19, U61.19, U62.19
/~shift1: RN2.9, U2.2, U5.19, U6.19, U9.19, U10.19, U11.1, U12.1, U15.1, U16.1
/~shift2: RN2.8, U2.4, U17.1, U18.1, U21.1, U22.1, U23.1, U24.1, U27.1, U28.1
/~shift4: RN2.7, U2.6, U29.19, U30.19, U33.19, U34.19, U35.19, U36.19, U39.19, U40.19
/~shift8: RN2.6, U2.8, U41.19, U42.19, U45.19, U46.19, U47.19, U48.19, U51.19, U52.19
/~shift16: RN2.4, U2.10, U4.2
/~shift_16_oe: RN2.2, U4.3, U53.19, U54.19, U57.19, U58.19, U59.19, U60.19, U63.19, U64.19
/~shift_left: RN1.9, U1.18, U2.13, U5.1, U6.1, U11.19, U12.19, U17.19, U18.19, U23.19, U24.19, U29.1, U30.1, U35.1, U36.1, U41.1, U42.1, U47.1, U48.1, U53.1, U54.1, U59.1, U60.1
/~shift_left': P1.191, U1.2
/~shift_oe: RN1.7, U1.11, U4.1, U4.4, U55.1, U56.1, U61.1, U62.1
/~shift_oe': P1.185, U1.9
/~shift_right: RN2.3, U2.12, U9.1, U10.1, U15.19, U16.19, U21.19, U22.19, U27.19, U28.19, U33.1, U34.1, U39.1, U40.1, U45.1, U46.1, U51.1, U52.1, U57.1, U58.1, U63.1, U64.1
GND: C1.2, C2.2, C3.2, C4.2, C5.2, C6.2, C7.2, C8.2, C9.2, C10.2, C11.2, C12.2, C13.2, C14.2, C15.2, C16.2, C17.2, C18.2, C19.2, C20.2, C21.2, C22.2, C23.2, C24.2, C25.2, C26.2, C27.2, C28.2, C29.2, C30.2, C31.2, C32.2, C33.2, C34.2, C35.2, C36.2, C37.2, C38.2, C39.2, C40.2, C41.2, C42.2, C43.2, C44.2, C45.2, C46.2, C47.2, C48.2, C49.2, C50.2, C51.2, C52.2, C53.2, C54.2, C55.2, C56.2, C57.2, C58.2, C59.2, C60.2, C61.2, C62.2, C63.2, C64.2, C65.2, C66.2, C67.2, P1.3, P1.9, P1.14, P1.20, P1.25, P1.31, P1.36, P1.42, P1.52, P1.58, P1.63, P1.69, P1.74, P1.80, P1.85, P1.91, P1.101, P1.107, P1.112, P1.118, P1.123, P1.129, P1.134, P1.140, P1.150, P1.156, P1.161, P1.167, P1.172, P1.178, P1.183, P1.189, U1.1, U1.10, U1.19, U2.7, U3.7, U4.7, U5.10, U6.10, U7.1, U7.10, U8.1, U8.10, U9.10, U10.10, U11.10, U12.9, U12.10, U13.10, U13.19, U14.10, U14.19, U15.10, U16.10, U17.10, U18.10, U19.10, U19.19, U20.10, U20.19, U21.10, U22.10, U23.10, U24.8, U24.9, U24.10, U25.10, U25.19, U26.10, U26.19, U27.10, U28.10, U29.10, U30.10, U31.1, U31.10, U32.1, U32.10, U33.10, U34.10, U35.10, U36.2, U36.3, U36.4, U36.5, U36.10, U37.1, U37.10, U38.1, U38.10, U39.10, U40.10, U41.10, U42.10, U43.1, U43.10, U44.1, U44.10, U45.10, U46.10, U47.10, U48.2, U48.3, U48.4, U48.5, U48.6, U48.7, U48.8, U48.9, U48.10, U49.1, U49.10, U50.1, U50.10, U51.10, U52.10, U53.10, U54.10, U55.10, U56.10, U57.10, U58.10, U59.2, U59.3, U59.4, U59.5, U59.6, U59.7, U59.8, U59.9, U59.10, U60.2, U60.3, U60.4, U60.5, U60.6, U60.7, U60.8, U60.9, U60.10, U61.10, U62.10, U63.10, U64.10
VCC: C1.1, C2.1, C3.1, C4.1, C5.1, C6.1, C7.1, C8.1, C9.1, C10.1, C11.1, C12.1, C13.1, C14.1, C15.1, C16.1, C17.1, C18.1, C19.1, C20.1, C21.1, C22.1, C23.1, C24.1, C25.1, C26.1, C27.1, C28.1, C29.1, C30.1, C31.1, C32.1, C33.1, C34.1, C35.1, C36.1, C37.1, C38.1, C39.1, C40.1, C41.1, C42.1, C43.1, C44.1, C45.1, C46.1, C47.1, C48.1, C49.1, C50.1, C51.1, C52.1, C53.1, C54.1, C55.1, C56.1, C57.1, C58.1, C59.1, C60.1, C61.1, C62.1, C63.1, C64.1, C65.1, C66.1, C67.1, P1.6, P1.17, P1.28, P1.39, P1.55, P1.66, P1.77, P1.88, P1.104, P1.115, P1.126, P1.137, P1.153, P1.164, P1.175, P1.186, RN1.5, RN1.10, RN2.5, RN2.10, U1.20, U2.14, U3.14, U4.14, U5.20, U6.20, U7.20, U8.20, U9.20, U10.20, U11.20, U12.20, U13.20, U14.20, U15.20, U16.20, U17.20, U18.20, U19.20, U20.20, U21.20, U22.20, U23.20, U24.20, U25.20, U26.20, U27.20, U28.20, U29.20, U30.20, U31.20, U32.20, U33.20, U34.20, U35.20, U36.20, U37.20, U38.20, U39.20, U40.20, U41.20, U42.20, U43.20, U44.20, U45.20, U46.20, U47.20, U48.20, U49.20, U50.20, U51.20, U52.20, U53.20, U54.20, U55.20, U56.20, U57.20, U58.20, U59.20, U60.20, U61.20, U62.20, U63.20, U64.20
